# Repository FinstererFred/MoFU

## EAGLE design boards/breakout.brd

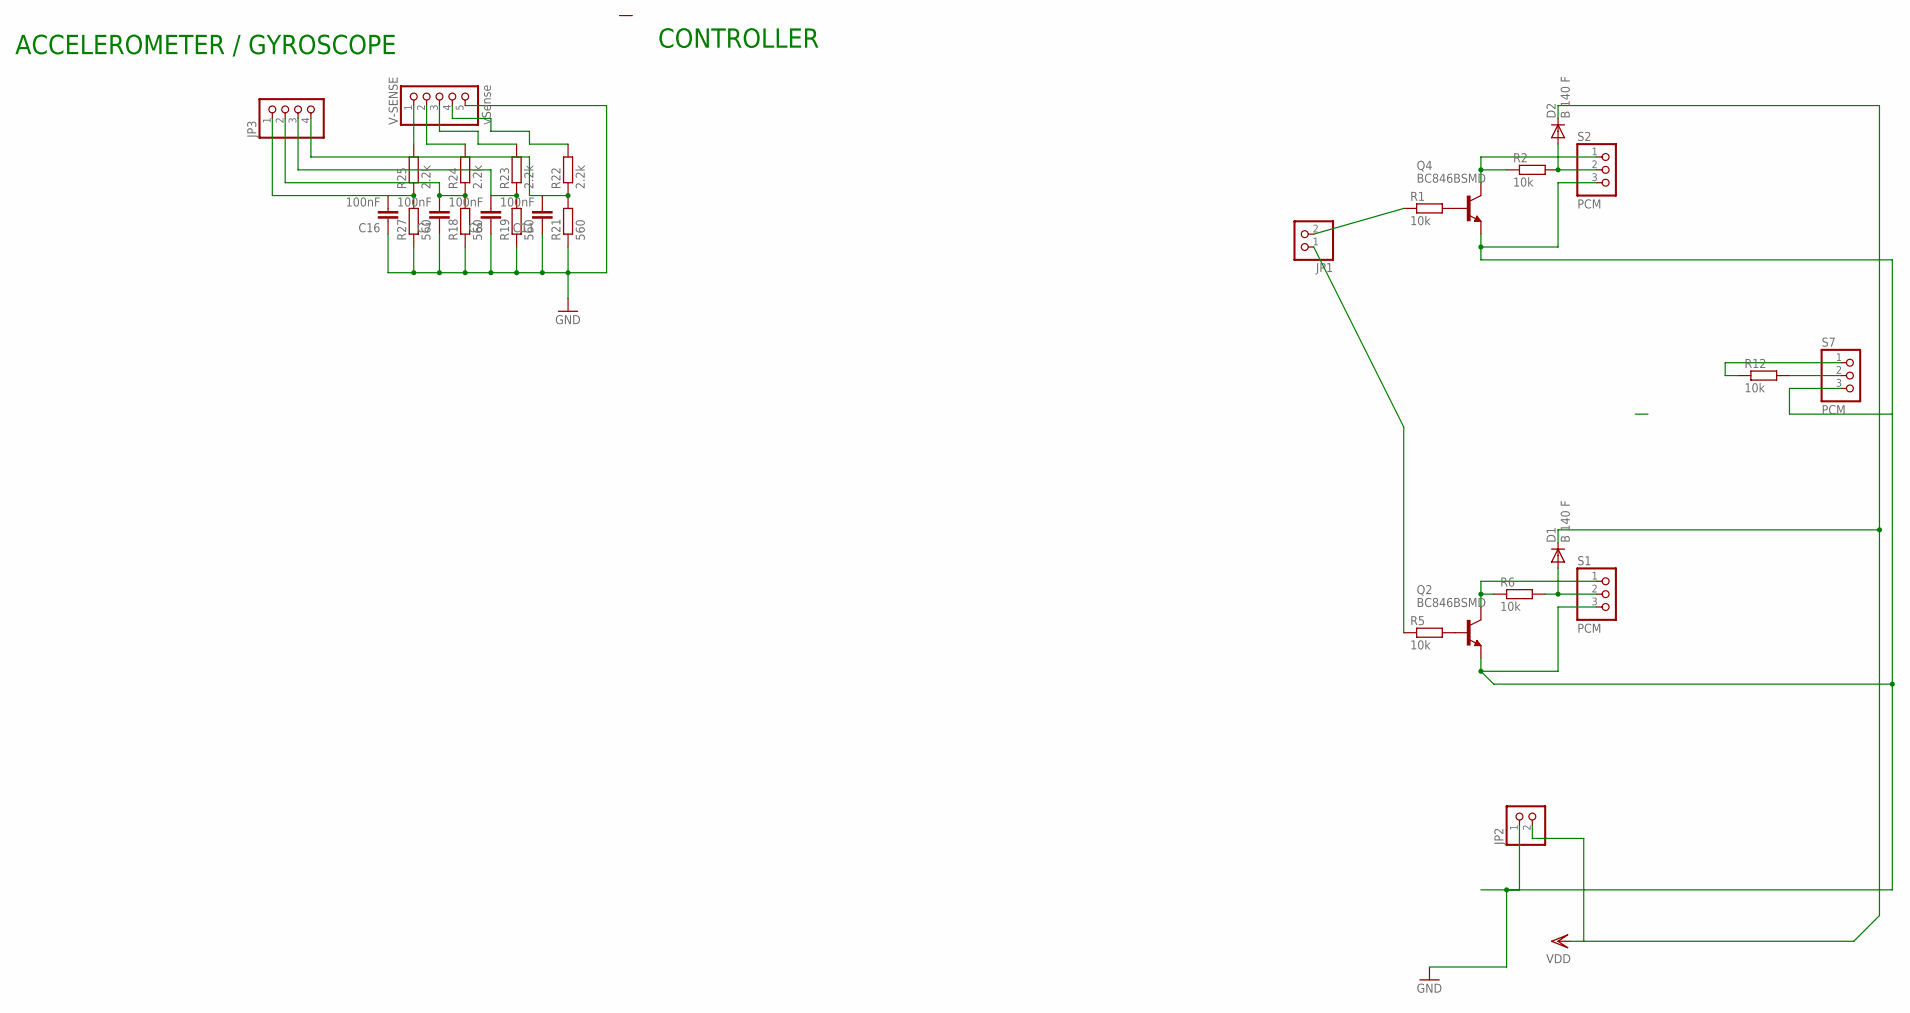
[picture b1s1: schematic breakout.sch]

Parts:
C7, C8, C11, C16: 100nF; C0603
D1, D2: B 140 F; SOD-123_MINI-SMA
JP1, JP2: PINHD-1X2; 1X02
JP3: PINHD-1X4; 1X04
Q2, Q4: BC846BSMD; SOT23
R1, R2, R5, R6, R12: 10k; R0603
R18, R19, R21, R27: 560; R0603
R22, R23, R24, R25: 2.2k; R0603
S1, S2, S7: PCM; 1X03
V-SENSE: vSense; 1X05/90

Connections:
GND: C7.1, C8.1, C11.1, C16.1, JP2.1, Q2.2 (E), Q4.2 (E), R18.1, R19.1, R21.1, R27.1, S1.3, S2.3, S7.3, V-SENSE.5
unnamed: Q4.1 (B), R1.2
unnamed: Q2.3 (C), R6.1, S1.1
unnamed: D1.A, R6.2, S1.2
unnamed: Q2.1 (B), R5.2
unnamed: Q4.3 (C), R2.1, S2.1
unnamed: D2.A, R2.2, S2.2
unnamed: R12.1, S7.1
unnamed: R12.2, S7.2
unnamed: JP1.2, R1.1
unnamed: JP1.1, R5.1
unnamed: R24.2, V-SENSE.2
unnamed: R23.2, V-SENSE.3
unnamed: R22.2, V-SENSE.4
unnamed: R25.2, V-SENSE.1
PB0: C16.2, JP3.1, R25.1, R27.2
PB1: C7.2, JP3.2, R18.2, R24.1
PB2: C8.2, JP3.3, R19.2, R23.1
PB3: C11.2, JP3.4, R21.2, R22.1
VDD: D1.C, D2.C, JP2.2

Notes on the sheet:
ACCELEROMETER / GYROSCOPE
CONTROLLER

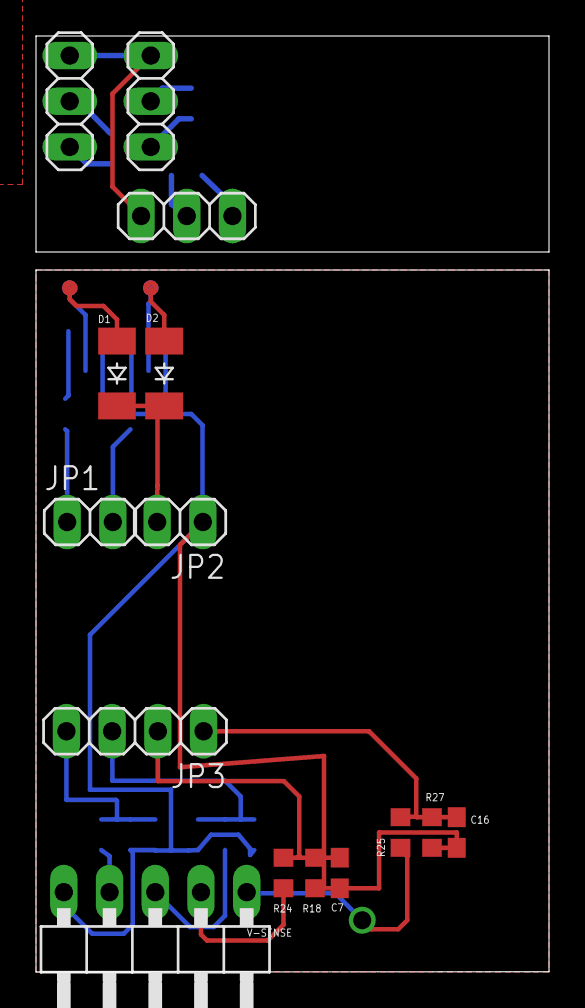
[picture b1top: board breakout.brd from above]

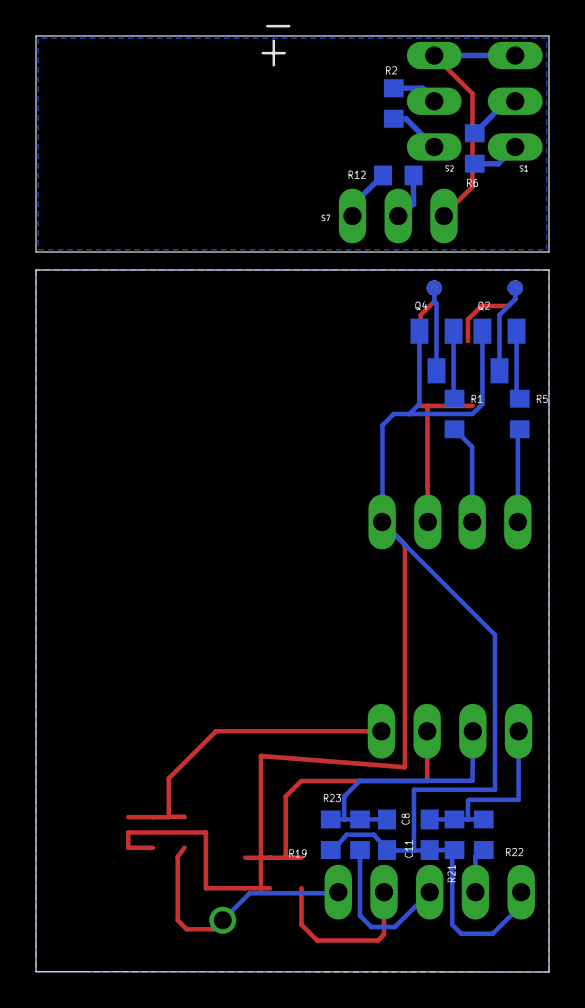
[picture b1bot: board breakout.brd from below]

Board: 8 copper layers, 28.5 x 52.0 mm, 28 parts (13 on the bottom side), 20 nets.

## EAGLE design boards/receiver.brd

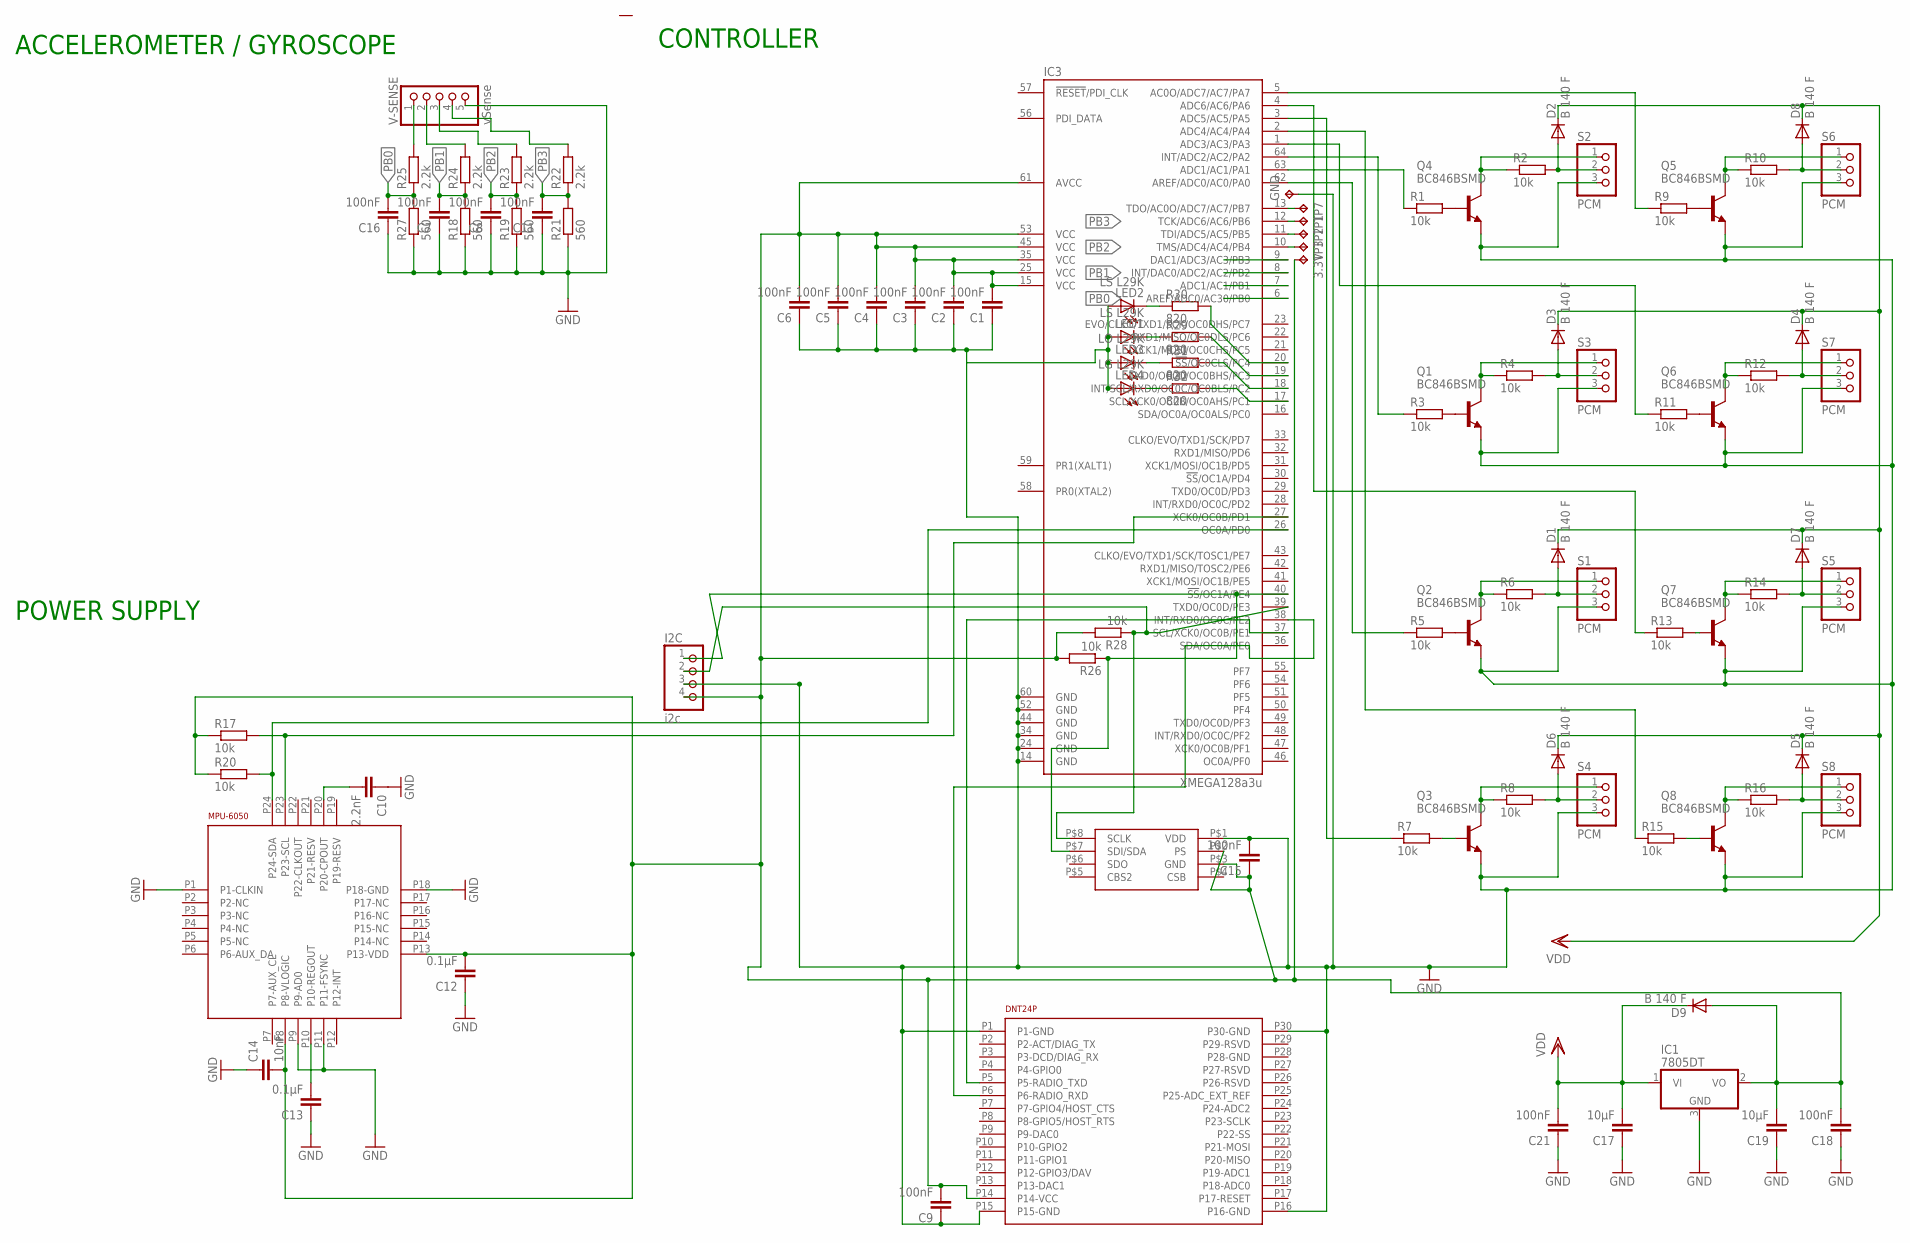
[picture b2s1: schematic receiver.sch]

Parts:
3.3V: TPTP08R; TP08R
C1, C2, C3, C4, C5, C6, C7, C8, C9, C11, C15, C16, C18, C21: 100nF; C0603
C10: 2.2nF; C0603
C12, C13: 0.1µF; C0603
C14: 10nF; C0603
C17, C19: 10µF; C0603
D1, D2, D3, D4, D5, D6, D7, D8, D9: B 140 F; SOD-123_MINI-SMA
GND: TPTP08R; TP08R
I2C: i2c; 1X04/90
IC1: 7805DT; TO252
IC3: XMEGA128a3u; TQFP-64
LED1, LED2: LS L29K; CHIP-LED0603
LED3: LO L29K; CHIP-LED0603
LED4: LG L29K; CHIP-LED0603
Q1, Q2, Q3, Q4, Q5, Q6, Q7, Q8: BC846BSMD; SOT23
R1, R2, R3, R4, R5, R6, R7, R8, R9, R10, R11, R12, R13, R14, R15, R16, R17, R20, R26, R28: 10k; R0603
R18, R19, R21, R27: 560; R0603
R22, R23, R24, R25: 2.2k; R0603
R29, R30, R31, R32: 820; R0603
S1, S2, S3, S4, S5, S6, S7, S8: PCM; 1X03
TP1, TP2, TP3, TP7: TPTP08R; TP08R
U$1: DNT24P_RADIO_MODULE
U$2: MS5611; 01BA03
U$3: MPU-6050_ACC_GYRO
V-SENSE: vSense; 1X05/90

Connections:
GND: C1.1, C2.1, C3.1, C4.1, C5.1, C6.1, C7.1, C8.1, C9.1, C10.1, C11.1, C12.1, C13.1, C14.1, C15.2, C16.1, C17.1, C18.1, C19.1, C21.1, GND.TP, I2C.3, IC1.3 (GND), IC3.14 (GND), IC3.24 (GND), IC3.34 (GND), IC3.44 (GND), IC3.52 (GND), IC3.60 (GND), LED1.A, LED2.A, LED3.A, LED4.A, Q1.2 (E), Q2.2 (E), Q3.2 (E), Q4.2 (E), Q5.2 (E), Q6.2 (E), Q7.2 (E), Q8.2 (E), R18.1, R19.1, R21.1, R27.1, S1.3, S2.3, S3.3, S4.3, S5.3, S6.3, S7.3, S8.3, U$1.P1 (P1-GND), U$1.P15 (P15-GND), U$1.P16 (P16-GND), U$1.P30 (P30-GND), U$2.P$1 (VDD), U$3.P1 (P1-CLKIN), U$3.P9 (P9-AD0), U$3.P11 (P11-FSYNC), U$3.P18 (P18-GND), V-SENSE.5
unnamed: Q4.1 (B), R1.2
unnamed: Q1.3 (C), R4.1, S3.1
unnamed: D3.A, R4.2, S3.2
unnamed: Q1.1 (B), R3.2
unnamed: Q2.3 (C), R6.1, S1.1
unnamed: D1.A, R6.2, S1.2
unnamed: Q2.1 (B), R5.2
unnamed: Q3.3 (C), R8.1, S4.1
unnamed: D6.A, R8.2, S4.2
unnamed: Q3.1 (B), R7.2
unnamed: Q5.3 (C), R10.1, S6.1
unnamed: D8.A, R10.2, S6.2
unnamed: Q5.1 (B), R9.2
unnamed: Q4.3 (C), R2.1, S2.1
unnamed: D2.A, R2.2, S2.2
unnamed: Q6.3 (C), R12.1, S7.1
unnamed: D4.A, R12.2, S7.2
unnamed: Q6.1 (B), R11.2
unnamed: Q7.3 (C), R14.1, S5.1
unnamed: D7.A, R14.2, S5.2
unnamed: Q7.1 (B), R13.2
unnamed: Q8.3 (C), R16.1, S8.1
unnamed: D5.A, R16.2, S8.2
unnamed: Q8.1 (B), R15.2
unnamed: IC3.63 (ADC1/AC1/PA1), R1.1
unnamed: IC3.64 (INT/ADC2/AC2/PA2), R3.1
unnamed: IC3.5 (AC0O/ADC7/AC7/PA7), R9.1
unnamed: IC3.4 (ADC6/AC6/PA6), R13.1
unnamed: IC3.62 (AREF/ADC0/AC0/PA0), R5.1
unnamed: IC3.1 (ADC3/AC3/PA3), R11.1
unnamed: IC3.2 (ADC4/AC4/PA4), R15.1
unnamed: IC3.3 (ADC5/AC5/PA5), R7.1
unnamed: IC3.37 (SCL/XCK0/OC0B/PE1), U$1.P5 (P5-RADIO_TXD)
unnamed: LED1.C, R29.1
unnamed: C10.2, U$3.P20 (P20-CPOUT)
unnamed: IC3.38 (INT/RXD0/OC0C/PE2), U$1.P6 (P6-RADIO_RXD)
unnamed: C13.2, U$3.P10 (P10-REGOUT)
unnamed: IC3.10 (TMS/ADC4/AC4/PB4), TP3.TP
unnamed: IC3.11 (TDI/ADC5/AC5/PB5), TP2.TP
unnamed: IC3.12 (TCK/ADC6/AC6/PB6), TP1.TP
unnamed: IC3.13 (TDO/AC0O/ADC7/AC7/PB7), TP7.TP
unnamed: R24.2, V-SENSE.2
unnamed: R23.2, V-SENSE.3
unnamed: R22.2, V-SENSE.4
unnamed: IC3.17 (SCL/XCK0/OC0B/OC0AHS/PC1), R32.2
unnamed: I2C.2, IC3.39 (TXD0/OC0D/PE3), R28.1, U$2.P$8 (SCLK)
unnamed: I2C.1, IC3.40 (!SS!/OC1A/PE4), R26.1, U$2.P$7 (SDI/SDA)
unnamed: IC3.18 (INT/SCL/RXD0/OC0C/OC0BLS/PC2), R31.2
unnamed: LED3.C, R31.1
unnamed: R25.2, V-SENSE.1
unnamed: LED4.C, R32.1
unnamed: IC3.19 (TXD0/OC0D/OC0BHS/PC3), R29.2
unnamed: LED2.C, R30.1
unnamed: IC3.20 (!SS!/OC0CLS/PC4), R30.2
PB0: C16.2, IC3.6 (AREF/ADC0/AC30/PB0), R25.1, R27.2
PB1: C7.2, IC3.7 (ADC1/AC1/PB1), R18.2, R24.1
PB2: C8.2, IC3.8 (INT/DAC0/ADC2/AC2/PB2), R19.2, R23.1
PB3: C11.2, IC3.9 (DAC1/ADC3/AC3/PB3), R21.2, R22.1
PF0: IC3.26 (OC0A/PD0), R20.2, U$3.P24 (P24-SDA)
PF1: IC3.27 (XCK0/OC0B/PD1), R17.2, U$3.P23 (P23-SCL)
VCC: 3.3V.TP, C1.2, C2.2, C3.2, C4.2, C5.2, C6.2, C9.2, C12.2, C14.2, C15.1, C18.2, C19.2, D9.A, I2C.4, IC1.2 (VO), IC3.15 (VCC), IC3.25 (VCC), IC3.35 (VCC), IC3.45 (VCC), IC3.53 (VCC), IC3.61 (AVCC), R17.1, R20.1, R26.2, R28.2, U$1.P14 (P14-VCC), U$2.P$2 (PS), U$2.P$3 (GND), U$3.P8 (P8-VLOGIC), U$3.P13 (P13-VDD)
VDD: C17.2, C21.2, D1.C, D2.C, D3.C, D4.C, D5.C, D6.C, D7.C, D8.C, D9.C, IC1.1 (VI)

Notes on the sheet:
ACCELEROMETER / GYROSCOPE
POWER SUPPLY
CONTROLLER

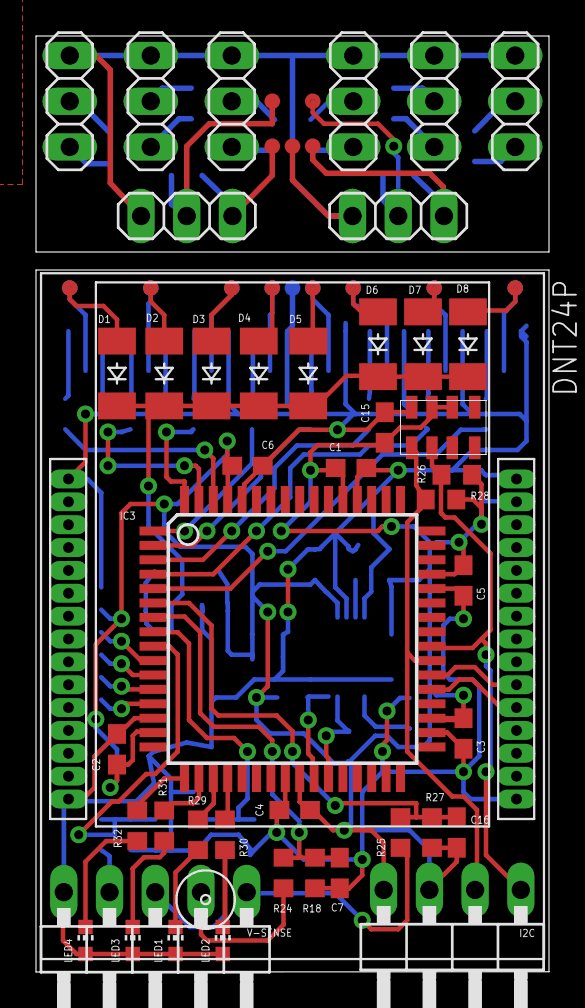
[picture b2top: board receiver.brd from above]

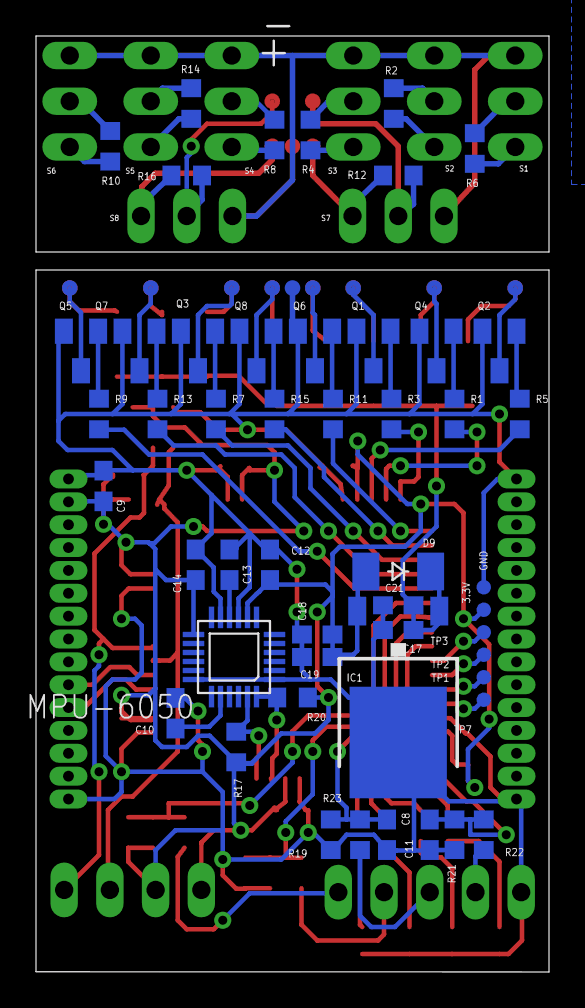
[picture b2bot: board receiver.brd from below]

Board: 8 copper layers, 28.5 x 52.0 mm, 94 parts (50 on the bottom side), 63 nets.

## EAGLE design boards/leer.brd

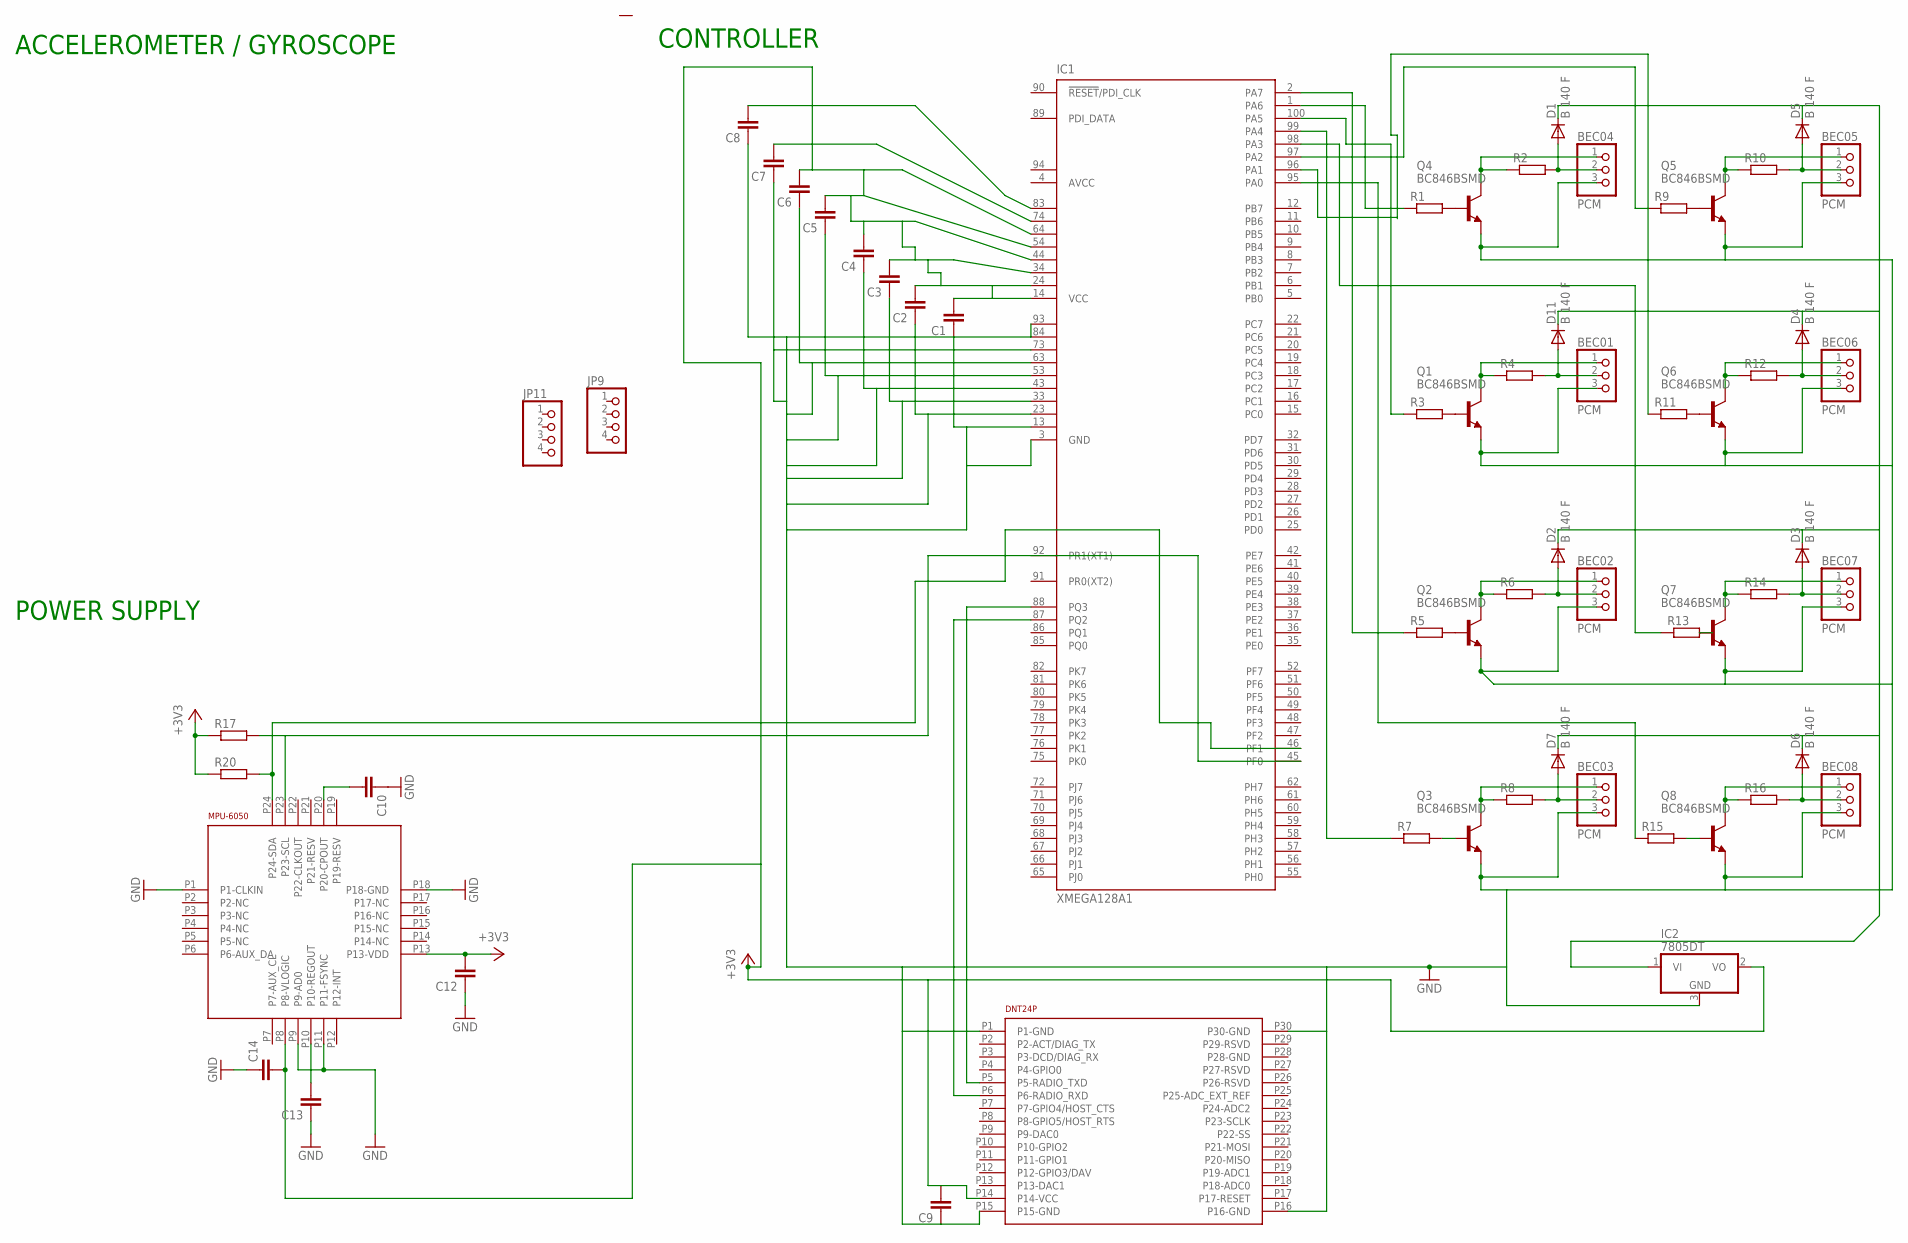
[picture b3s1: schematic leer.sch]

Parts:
BEC01, BEC02, BEC03, BEC04, BEC05, BEC06, BEC07, BEC08: PCM; 1X03
C1, C2, C3, C4, C5, C6, C7, C8, C9, C10, C12, C13, C14: CC0603; C0603
D1, D2, D3, D4, D5, D6, D7, D11: B 140 F; SOD-123_MINI-SMA
IC1: XMEGA128A1; TQFP100
IC2: 7805DT; TO252
JP9, JP11: PINHD-1X4; 1X04
Q1, Q2, Q3, Q4, Q5, Q6, Q7, Q8: BC846BSMD; SOT23
R1, R2, R3, R4, R5, R6, R7, R8, R9, R10, R11, R12, R13, R14, R15, R16, R17, R20: RR0603; R0603
U$1: DNT24P_RADIO_MODULE
U$3: MPU-6050_ACC_GYRO

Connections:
+3V3: C1.2, C2.2, C3.2, C4.2, C5.2, C6.2, C7.2, C8.2, C9.2, C12.2, C14.2, IC1.14 (VCC), IC1.24 (VCC1), IC1.34 (VCC2), IC1.44 (VCC3), IC1.54 (VCC4), IC1.64 (VCC5), IC1.74 (VCC6), IC1.83 (VCC7), IC2.2 (VO), R17.1, R20.1, U$1.P14 (P14-VCC), U$3.P8 (P8-VLOGIC), U$3.P13 (P13-VDD)
AVCC: IC1.4 (AVCC)
AVCC1: IC1.94 (AVCC1)
GND: BEC01.3, BEC02.3, BEC03.3, BEC04.3, BEC05.3, BEC06.3, BEC07.3, BEC08.3, C1.1, C2.1, C3.1, C4.1, C5.1, C6.1, C7.1, C8.1, C9.1, C10.1, C12.1, C13.1, C14.1, IC1.3 (GND), IC1.13 (GND1), IC1.23 (GND2), IC1.33 (GND3), IC1.43 (GND4), IC1.53 (GND5), IC1.63 (GND6), IC1.73 (GND7), IC1.84 (GND8), IC1.93 (GND9), IC2.3 (GND), Q1.2 (E), Q2.2 (E), Q3.2 (E), Q4.2 (E), Q5.2 (E), Q6.2 (E), Q7.2 (E), Q8.2 (E), U$1.P1 (P1-GND), U$1.P15 (P15-GND), U$1.P16 (P16-GND), U$1.P30 (P30-GND), U$3.P1 (P1-CLKIN), U$3.P9 (P9-AD0), U$3.P11 (P11-FSYNC), U$3.P18 (P18-GND)
unnamed: Q4.1 (B), R1.2
unnamed: BEC01.1, Q1.3 (C), R4.1
unnamed: BEC01.2, D11.A, R4.2
unnamed: Q1.1 (B), R3.2
unnamed: BEC02.1, Q2.3 (C), R6.1
unnamed: BEC02.2, D2.A, R6.2
unnamed: Q2.1 (B), R5.2
unnamed: BEC03.1, Q3.3 (C), R8.1
unnamed: BEC03.2, D7.A, R8.2
unnamed: Q3.1 (B), R7.2
unnamed: BEC05.1, Q5.3 (C), R10.1
unnamed: BEC05.2, D5.A, R10.2
unnamed: Q5.1 (B), R9.2
unnamed: BEC04.1, Q4.3 (C), R2.1
unnamed: BEC04.2, D1.A, R2.2
unnamed: BEC06.1, Q6.3 (C), R12.1
unnamed: BEC06.2, D4.A, R12.2
unnamed: Q6.1 (B), R11.2
unnamed: BEC07.1, Q7.3 (C), R14.1
unnamed: BEC07.2, D3.A, R14.2
unnamed: Q7.1 (B), R13.2
unnamed: BEC08.1, Q8.3 (C), R16.1
unnamed: BEC08.2, D6.A, R16.2
unnamed: Q8.1 (B), R15.2
unnamed: IC1.1 (PA6), R1.1
unnamed: IC1.100 (PA5), R3.1
unnamed: IC1.97 (PA2), R9.1
unnamed: IC1.96 (PA1), R11.1
unnamed: IC1.2 (PA7), R5.1
unnamed: IC1.98 (PA3), R13.1
unnamed: IC1.99 (PA4), R7.1
unnamed: IC1.95 (PA0), R15.1
unnamed: IC1.88 (PQ3), U$1.P5 (P5-RADIO_TXD)
unnamed: D1.C, D2.C, D3.C, D4.C, D5.C, D6.C, D7.C, D11.C, IC2.1 (VI)
unnamed: C10.2, U$3.P20 (P20-CPOUT)
unnamed: IC1.87 (PQ2), U$1.P6 (P6-RADIO_RXD)
unnamed: C13.2, U$3.P10 (P10-REGOUT)
PF0: IC1.46 (PF1), R20.2, U$3.P24 (P24-SDA)
PF1: IC1.45 (PF0), R17.2, U$3.P23 (P23-SCL)

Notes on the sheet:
ACCELEROMETER / GYROSCOPE
POWER SUPPLY
CONTROLLER

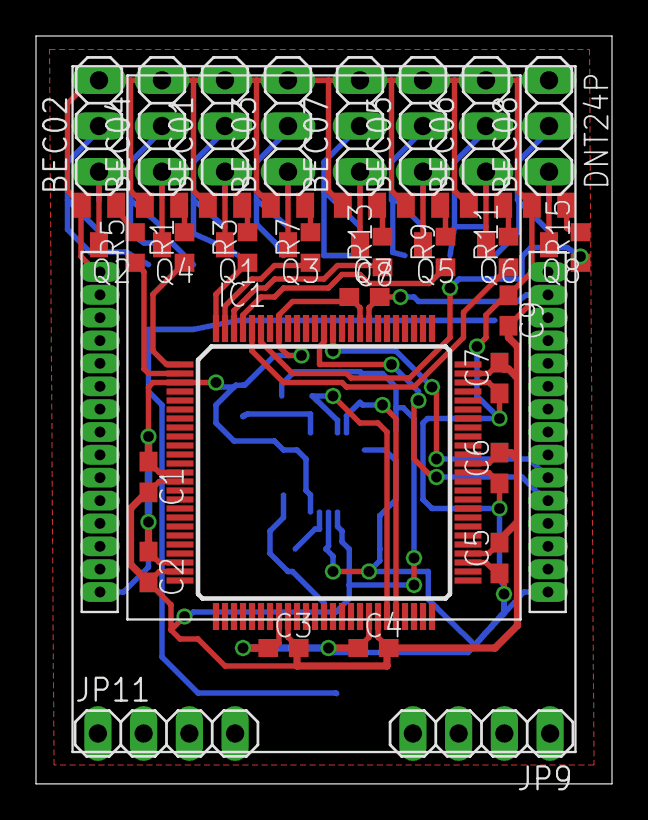
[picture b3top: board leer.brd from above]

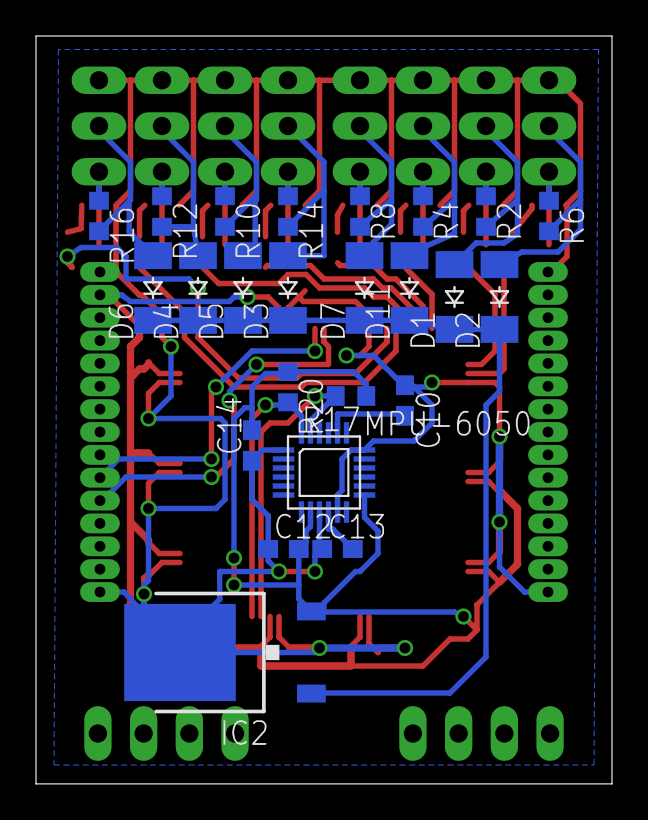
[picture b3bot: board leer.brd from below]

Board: 2 copper layers, 32.0 x 41.5 mm, 61 parts (24 on the bottom side), 41 nets.

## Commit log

2014-11-06 Initial commit of board files
2014-11-06 forgot schematic
2014-11-06 modified receiver layout
2014-11-06 Update layout
2014-11-11 New Version of Receiver Layout, with two Boards
2014-11-13 - more board changes - we-direkt design rule check modifications - made editable with eagle lite again
2014-11-13 Removed old Layout Versions, as they are obsolete
2014-11-13 Board passes drc checks for we-direkt and itead now
2014-11-14 Updated Board with Voltage-Sensing Circuit
2014-11-17 Added Barometer
2014-11-17 Changed location of barometer
2014-11-17 renamed files to receiver
2014-11-18 Layout changes, all connections are routed now
2014-11-19 rerouted some wires
2014-11-20 Added some passives for the voltage regulator.
2014-11-21 Added some status leds
2014-11-26 Added another led, proper resistor values for voltage dividers, layout of silkscreen
2014-11-27 Added simplified breakout board for testing purposes
2014-11-28 Made some minor changes
